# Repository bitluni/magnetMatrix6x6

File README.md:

# project video 
https://youtu.be/L2J_eNgjxio

# prerquisites 
Ardino IDE https://www.arduino.cc/en/software

ATTiny library https://github.com/SpenceKonde/megaTinyCore

UPDI progammer https://github.com/ElTangas/jtag2updi

# Parts (affiliate)
ATTiny1604

Magnet Connectors https://aliexpress.bitluni.net/magnetConnectors

WS2812D 5 & 8mm https://aliexpress.bitluni.net/ws2812d

# Support
https://paypal.me/bitluni

https://github.com/sponsors/bitluni

https://patreon.com/bitluni

have fun & thx for the support

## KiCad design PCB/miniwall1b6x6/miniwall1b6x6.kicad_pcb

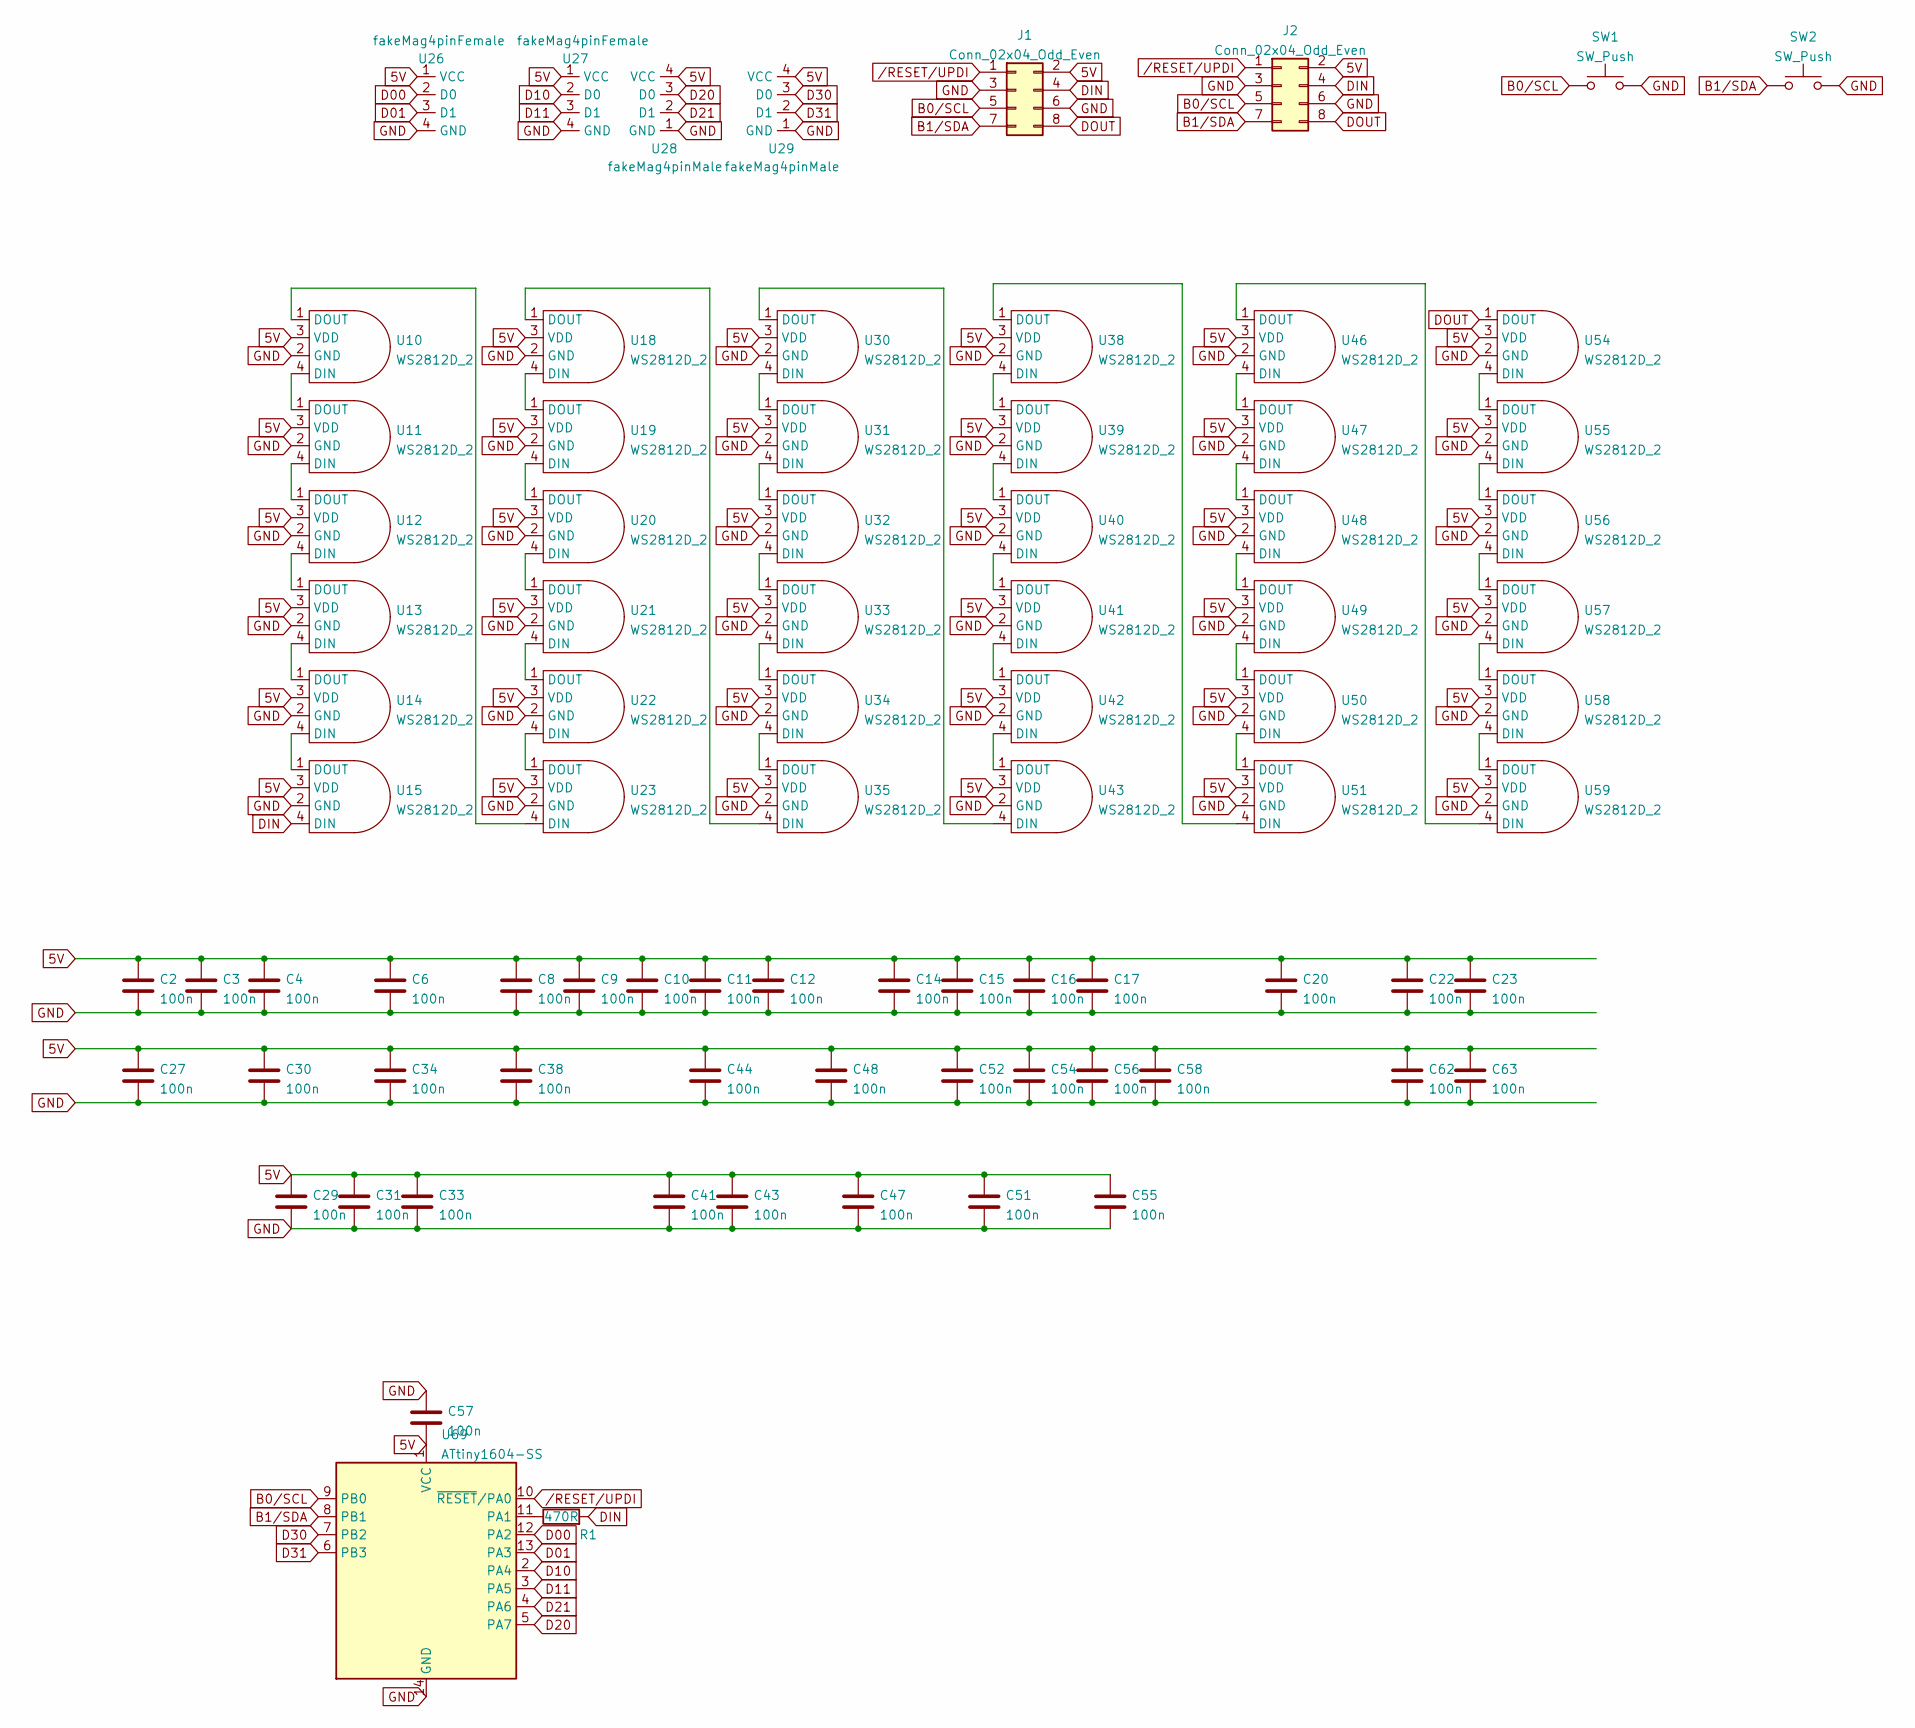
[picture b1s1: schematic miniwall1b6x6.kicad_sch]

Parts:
C2, C3, C4, C6, C8, C9, C10, C11, C12, C14, C15, C16, C17, C20, C22, C23, C27, C29, C30, C31, C33, C34, C38, C41, C43, C44, C47, C48, C51, C52, C54, C55, C56, C57, C58, C62, C63: 100n; C_0603_1608Metric
J1, J2: Conn_02x04_Odd_Even; PinHeader_2x04_P2.54mm_Vertical_SMD; MPN 54202-S08-04LF
R1: 470R; R_0603_1608Metric
SW1, SW2: SW_Push; SMD_ButtonC354946; MPN TSA343G00-250J2
U10, U11, U12, U13, U14, U15, U18, U19, U20, U21, U22, U23, U30, U31, U32, U33, U34, U35, U38, U39, U40, U41, U42, U43, U46, U47, U48, U49, U50, U51, U54, U55, U56, U57, U58, U59: WS2812D_2; WS2812DwideC
U26, U27: fakeMag4pinFemale; fakemag4pin90degFemale; MPN MG0422F-RA
U28, U29: fakeMag4pinMale; fakemag4pin90degMale; MPN MG0422F-RA
U69: ATtiny1604-SS; SOIC-14_3.9x8.7mm_P1.27mm

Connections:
5V: C2.1, C3.1, C4.1, C6.1, C8.1, C9.1, C10.1, C11.1, C12.1, C14.1, C15.1, C16.1, C17.1, C20.1, C22.1, C23.1, C27.1, C29.1, C30.1, C31.1, C33.1, C34.1, C38.1, C41.1, C43.1, C44.1, C47.1, C48.1, C51.1, C52.1, C54.1, C55.1, C56.1, C57.2, C58.1, C62.1, C63.1, J1.2, J2.2, U10.3 (VDD), U11.3 (VDD), U12.3 (VDD), U13.3 (VDD), U14.3 (VDD), U15.3 (VDD), U18.3 (VDD), U19.3 (VDD), U20.3 (VDD), U21.3 (VDD), U22.3 (VDD), U23.3 (VDD), U26.1 (VCC), U27.1 (VCC), U28.4 (VCC), U29.4 (VCC), U30.3 (VDD), U31.3 (VDD), U32.3 (VDD), U33.3 (VDD), U34.3 (VDD), U35.3 (VDD), U38.3 (VDD), U39.3 (VDD), U40.3 (VDD), U41.3 (VDD), U42.3 (VDD), U43.3 (VDD), U46.3 (VDD), U47.3 (VDD), U48.3 (VDD), U49.3 (VDD), U50.3 (VDD), U51.3 (VDD), U54.3 (VDD), U55.3 (VDD), U56.3 (VDD), U57.3 (VDD), U58.3 (VDD), U59.3 (VDD), U69.1 (VCC)
B0/SCL: J1.5, J2.5, SW1.1, U69.9 (PB0)
B1/SDA: J1.7, J2.7, SW2.1, U69.8 (PB1)
D00: U26.2 (D0), U69.12 (PA2)
D01: U26.3 (D1), U69.13 (PA3)
D10: U27.2 (D0), U69.2 (PA4)
D11: U27.3 (D1), U69.3 (PA5)
D20: U28.3 (D0), U69.5 (PA7)
D21: U28.2 (D1), U69.4 (PA6)
D30: U29.3 (D0), U69.7 (PB2)
D31: U29.2 (D1), U69.6 (PB3)
DIN: J1.4, J2.4, R1.2, U15.4 (DIN)
DOUT: J1.8, J2.8, U54.1 (DOUT)
GND: C2.2, C3.2, C4.2, C6.2, C8.2, C9.2, C10.2, C11.2, C12.2, C14.2, C15.2, C16.2, C17.2, C20.2, C22.2, C23.2, C27.2, C29.2, C30.2, C31.2, C33.2, C34.2, C38.2, C41.2, C43.2, C44.2, C47.2, C48.2, C51.2, C52.2, C54.2, C55.2, C56.2, C57.1, C58.2, C62.2, C63.2, J1.3, J1.6, J2.3, J2.6, SW1.2, SW2.2, U10.2 (GND), U11.2 (GND), U12.2 (GND), U13.2 (GND), U14.2 (GND), U15.2 (GND), U18.2 (GND), U19.2 (GND), U20.2 (GND), U21.2 (GND), U22.2 (GND), U23.2 (GND), U26.4 (GND), U27.4 (GND), U28.1 (GND), U29.1 (GND), U30.2 (GND), U31.2 (GND), U32.2 (GND), U33.2 (GND), U34.2 (GND), U35.2 (GND), U38.2 (GND), U39.2 (GND), U40.2 (GND), U41.2 (GND), U42.2 (GND), U43.2 (GND), U46.2 (GND), U47.2 (GND), U48.2 (GND), U49.2 (GND), U50.2 (GND), U51.2 (GND), U54.2 (GND), U55.2 (GND), U56.2 (GND), U57.2 (GND), U58.2 (GND), U59.2 (GND), U69.14 (GND)
unnamed: U10.4 (DIN), U11.1 (DOUT)
unnamed: U10.1 (DOUT), U23.4 (DIN)
unnamed: U11.4 (DIN), U12.1 (DOUT)
unnamed: U12.4 (DIN), U13.1 (DOUT)
unnamed: U13.4 (DIN), U14.1 (DOUT)
unnamed: U14.4 (DIN), U15.1 (DOUT)
unnamed: U18.4 (DIN), U19.1 (DOUT)
unnamed: U18.1 (DOUT), U35.4 (DIN)
unnamed: U19.4 (DIN), U20.1 (DOUT)
unnamed: U20.4 (DIN), U21.1 (DOUT)
unnamed: U21.4 (DIN), U22.1 (DOUT)
unnamed: U22.4 (DIN), U23.1 (DOUT)
unnamed: U30.4 (DIN), U31.1 (DOUT)
unnamed: U30.1 (DOUT), U43.4 (DIN)
unnamed: U31.4 (DIN), U32.1 (DOUT)
unnamed: U32.4 (DIN), U33.1 (DOUT)
unnamed: U33.4 (DIN), U34.1 (DOUT)
unnamed: U34.4 (DIN), U35.1 (DOUT)
unnamed: U38.4 (DIN), U39.1 (DOUT)
unnamed: U38.1 (DOUT), U51.4 (DIN)
unnamed: U39.4 (DIN), U40.1 (DOUT)
unnamed: U40.4 (DIN), U41.1 (DOUT)
unnamed: U41.4 (DIN), U42.1 (DOUT)
unnamed: U42.4 (DIN), U43.1 (DOUT)
unnamed: U46.4 (DIN), U47.1 (DOUT)
unnamed: U46.1 (DOUT), U59.4 (DIN)
unnamed: U47.4 (DIN), U48.1 (DOUT)
unnamed: U48.4 (DIN), U49.1 (DOUT)
unnamed: U49.4 (DIN), U50.1 (DOUT)
unnamed: U50.4 (DIN), U51.1 (DOUT)
unnamed: U54.4 (DIN), U55.1 (DOUT)
unnamed: U55.4 (DIN), U56.1 (DOUT)
unnamed: U56.4 (DIN), U57.1 (DOUT)
unnamed: U57.4 (DIN), U58.1 (DOUT)
unnamed: U58.4 (DIN), U59.1 (DOUT)
unnamed: R1.1, U69.11 (PA1)
/RESET/UPDI: J1.1, J2.1, U69.10 (~RESET/PA0)

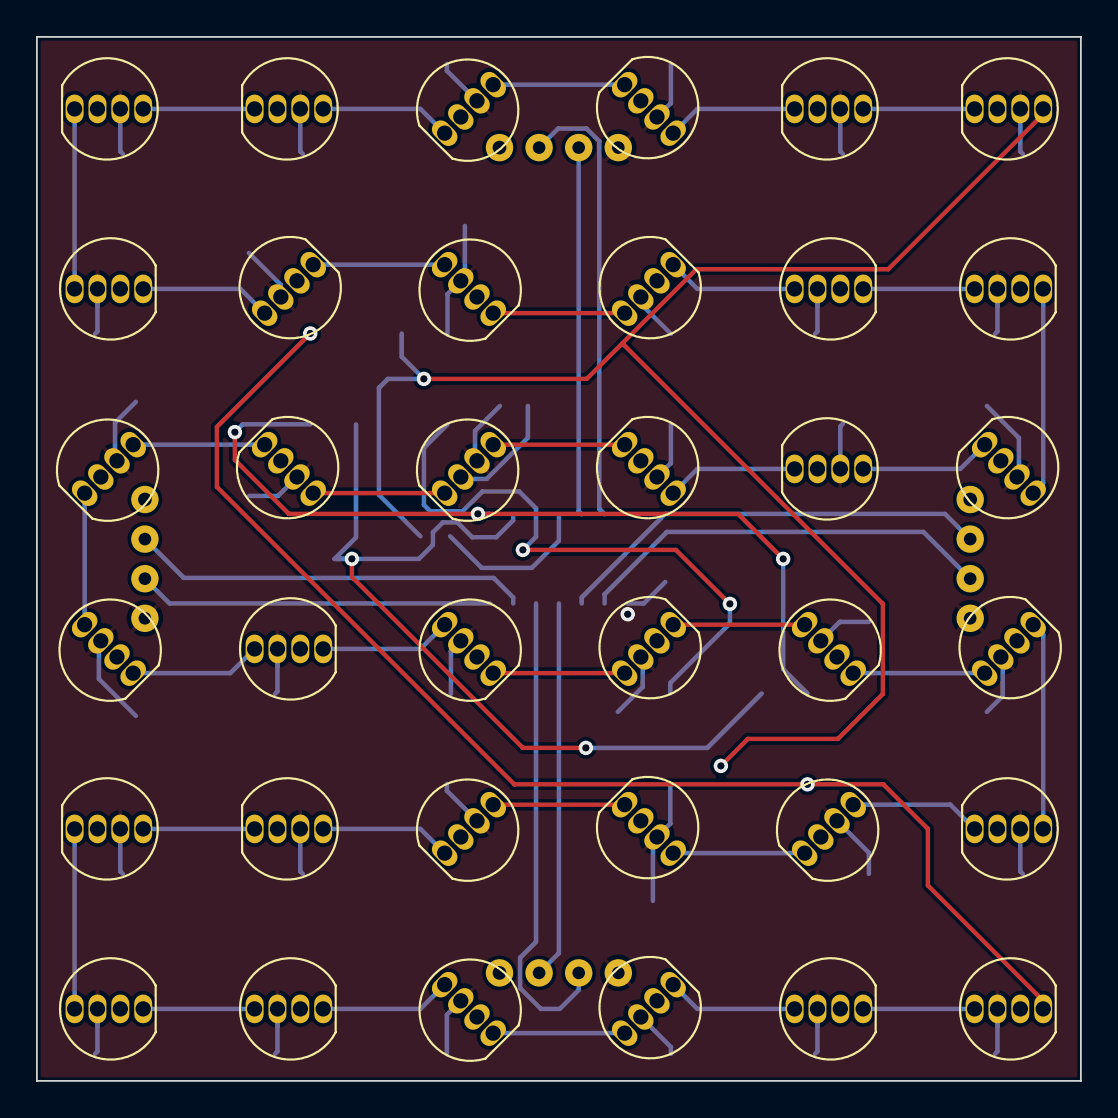
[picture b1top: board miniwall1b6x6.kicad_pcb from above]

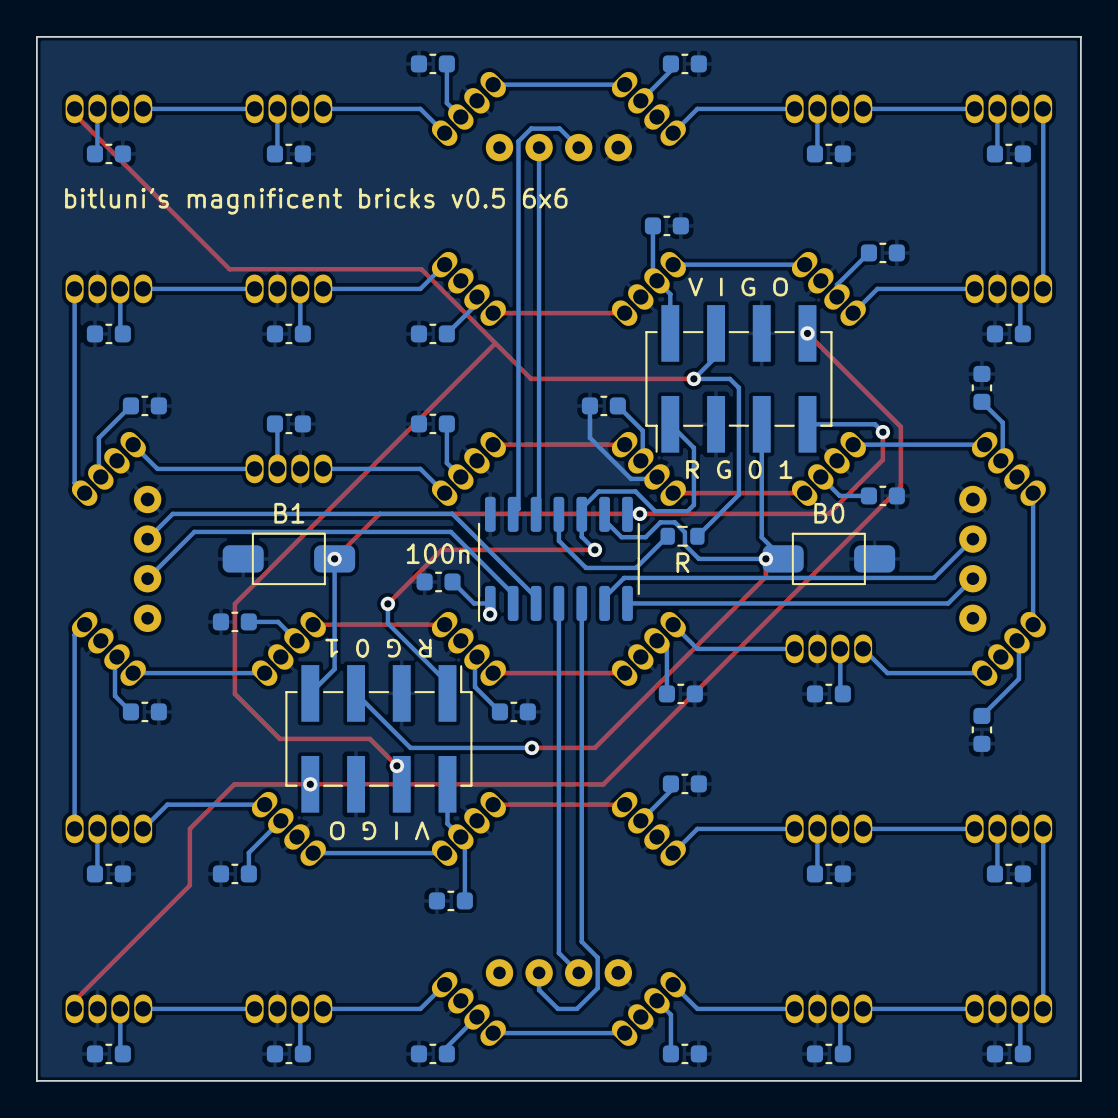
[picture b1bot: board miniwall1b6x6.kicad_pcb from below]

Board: 2 copper layers, 58.0 x 58.0 mm, 83 parts (43 on the bottom side), 51 nets.

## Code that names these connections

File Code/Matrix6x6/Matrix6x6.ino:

#include <tinyNeoPixel_Static.h>

const int ledPin = PIN_PA1;
const unsigned char xres = 6;
const unsigned char yres = 6;
const int ledBufferSize = xres * yres * 3;
unsigned char ledBuffer[ledBufferSize];

const int pins[4][2] = {{PIN_PA2, PIN_PA3}, {PIN_PA4, PIN_PA5}, {PIN_PA6, PIN_PA7}, {PIN_PB2, PIN_PB3}};


tinyNeoPixel leds = tinyNeoPixel(xres * yres, ledPin, NEO_GRB, ledBuffer);

int dimm = 4;

void fill(int i)
{
  for(int y = 0; y < yres; y++)
    for(int x = 0; x < xres; x++)
    {
      int cx = y & 1 ? xres - 1 - x : x;
      ledBuffer[(x + y * xres) * 3 + 0] = (((cx + i)%xres) * 256 / xres) >> dimm;  
      ledBuffer[(x + y * xres) * 3 + 1] = (((y + i)%yres) * 256 / yres) >> dimm;  
      ledBuffer[(x + y * xres) * 3 + 2] = ((xres - max(cx,y) - 1) * 256 / xres) >> dimm;
    }
}
void clear()
{
  for(int i = 0; i < xres * yres * 3; i++)
      ledBuffer[i] = 0;
}

int addr(int x, int y)
{
  if(y & 1)
    return (y * xres + xres - 1 - x) * 3;
  else
    return (y * xres + x) * 3;
}

void showSides(int i, int sides)
{
  clear();
  for(int x = 0; x < xres; x++)
  {
    if((sides & 1) == 0)
    if(((3-x) & 3) == (i & 3))
    {
      ledBuffer[(x + 0) * 3 + 0] = 255 >> dimm;
      ledBuffer[(x + 0) * 3 + 1] = 255 >> dimm;
      ledBuffer[(x + 0) * 3 + 2] = 255 >> dimm;
    }
    if((sides & 4) == 0)
    if(((3-x) & 3) == (i & 3))
    {
      ledBuffer[(x + (yres - 1) * xres) * 3 + 0] = 255 >> dimm;
      ledBuffer[(x + (yres - 1) * xres) * 3 + 1] = 255 >> dimm;
      ledBuffer[(x + (yres - 1) * xres) * 3 + 2] = 255 >> dimm;
    }
  }
  for(int y = 0; y < yres; y++)
  {
    if((sides & 2) == 0)
    if((y & 3) == (i & 3))
    {
      ledBuffer[addr(0, y) + 0] = 255 >> dimm;
      ledBuffer[addr(0, y) + 1] = 255 >> dimm;
      ledBuffer[addr(0, y) + 2] = 255 >> dimm;
    }
    if((sides & 8) == 0)
    if(((3 - y) & 3) == (i & 3))
    {
      ledBuffer[addr(xres - 1, y) + 0] = 255 >> dimm;
      ledBuffer[addr(xres - 1, y) + 1] = 255 >> dimm;
      ledBuffer[addr(xres - 1, y) + 2] = 255 >> dimm;
    }
  }
}

void setup() 
{
  //led
  pinMode(ledPin, OUTPUT);
  //magnet connectors
  pinMode(pins[0][0], INPUT_PULLUP);
  pinMode(pins[0][1], OUTPUT); digitalWrite(pins[0][1], 0);
  pinMode(pins[1][0], INPUT_PULLUP);
  pinMode(pins[1][1], OUTPUT); digitalWrite(pins[1][1], 0);
  pinMode(pins[2][0], INPUT_PULLUP);
  pinMode(pins[2][1], OUTPUT); digitalWrite(pins[2][1], 0);
  pinMode(pins[3][1], INPUT_PULLUP);
  pinMode(pins[3][0], OUTPUT); digitalWrite(pins[3][0], 0);
  //buttons
  pinMode(PIN_PB0, INPUT_PULLUP);
  pinMode(PIN_PB1, INPUT_PULLUP);

  fill(0);
}

void loop() 
{
  static int i = 0;
  int sides = 
    (digitalRead(pins[0][0]) ? 0 : 1) + 
    (digitalRead(pins[1][0]) ? 0 : 2) + 
    (digitalRead(pins[2][0]) ? 0 : 4) + 
    (digitalRead(pins[3][1]) ? 0 : 8);
  int buttons = 
    (digitalRead(PIN_PB0) ? 0 : 1) + 
    (digitalRead(PIN_PB1) ? 0 : 2);
  static int oldButtons = 0;
  if(oldButtons != 0 && buttons == 0)
    dimm = (dimm + 1) % 6;
  oldButtons = buttons;
  if(sides)
    showSides(i, sides);
  else
    fill(i);
  i++;
  leds.show();
  delay(50);
}

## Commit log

2024-10-12 readme
2024-10-12 docs
2024-10-12 formatting
